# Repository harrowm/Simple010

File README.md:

# Simple010

A 68010 single-board computer based on the [rosco_m68k r2](https://github.com/rosco-m68k/rosco_m68k) design. Simple010 replaces the six discrete glue-logic ICs from that design with a single **ATF1508AS PLCC84 CPLD**, reducing board complexity while adding hardware SPI acceleration for SD card access.

## Hardware overview

| Item | Detail |
|------|--------|
| CPU | Motorola MC68010P at 10 MHz |
| RAM | 1 MB — two AS6C4008-55PCN SRAMs (even/odd byte lanes) |
| ROM | Two SST39SF040 4 Mb flash (even/odd byte lanes) |
| CPLD | ATF1508AS PLCC84 — replaces IC2/IC3/IC4/IC5/IC6/IC7 from rosco_m68k r2 |
| USB/serial | MCP2221A — USB-CDC serial to UART A. The original rosco_m68k board has two UARTs A and B. However, the code for two UARTs won't fit into the CPLD, so a cheaper one-channel USB-to-serial chip is used. |
| PCB | 4-layer, 100 × 100 mm, JLCPCB stackup (F.Cu / GND / PWR / B.Cu) |

### Memory map

| Range | Device |
|-------|--------|
| `$000000–$0FFFFF` | 1 MB SRAM |
| `$100000–$DFFFFF` | Expansion bus (DTACK from `LGEXP`) |
| `$E00000–$EFFFFF` | Flash ROM |
| `$F00000–$FFFFFF` | I/O — CPLD UART at `$F00000`, register select via A1–A4 |

### CPLD functional blocks

The CPLD (`code/cpld/cpld.v`) implements:

1. **Glue logic** — HALT/RESET open-drain drivers, CPU-space gating, boot flag
2. **Address decoder** — RAM, ROM, expansion, and I/O selects; DTACK; WR
3. **Watchdog** — 16-cycle timeout, asserts BERR open-drain
4. **UART A** — fixed 115200 8N1, XR68C681-compatible register map
5. **GPIO / OPR** — XR68C681 output port emulation; drives SPI CS, LEDs, MOSI, SCK
6. **SPI RX accelerator** — hardware-assisted SD card byte receive at ~1.843 MHz
7. **Interrupt priority encoder** — replaces 74LS148; encodes IRQ2/3/5/6 + UART RX into IPL2:1:0

Resource utilisation: **122/128 macro cells (95%)**.

## Repository layout

```
design/
  Simple010/            KiCad 10 schematic and PCB (1 MB SRAM)
    Simple010.kicad_sch   top-level (references four sub-sheets)
    CPU.kicad_sch         MC68010P, oscillator, expansion connector
    Memory.kicad_sch      SRAM, ROM, write-enable jumper
    CPLD.kicad_sch        ATF1508AS, JTAG header, LEDs, pull-ups
    USB.kicad_sch         MCP2221A, SD card, reset supervisor, power LEDs
    production/           Gerbers, BOM, position file
  Simple010-16/         KiCad 10 schematic and PCB (16 MB SRAM variant)
  datasheets/           component datasheets and parts index (INDEX.md)

code/cpld/       ATF1508AS Verilog RTL and testbench
  cpld.v                RTL source with //PIN: preassignment comments
  tb_cpld.v             testbench (120 assertions)
  build.sh              synthesis → fit → pin check → simulation
  cpld.jed              program this into the device
  cpld.fit / cpld.pin   fitter log and pin placement

rosco/           rosco_m68k firmware (git clone), modified for Simple010
```

## CPLD build

Requires [`atf15xx_yosys`](https://github.com/hoglet67/atf15xx_yosys.git) cloned into `~/atf15xx_yosys`, and `iverilog`/`vvp` on PATH.

```sh
cd code/cpld && ./build.sh
```

Expected output: `122/128 MCs used` and `120/120 tests passed`.

To run the testbench without re-synthesising:

```sh
cd code/cpld && iverilog -DSIMULATION -o tb_cpld tb_cpld.v cpld.v && vvp tb_cpld
```

The `-DSIMULATION` flag is required — without it 2 of 120 tests fail due to a cross-clock-domain handshake that behaves differently under deterministic simulation timing.

## Firmware

The firmware is the standard rosco_m68k r2 firmware cloned into `rosco/`, with minimal changes for Simple010 hardware.

The rosco directory is a clone of [rosco-m68k/rosco_m68k](https://github.com/rosco-m68k/rosco_m68k). Simple010 changes are on the `develop` branch, pushed to a fork at [harrowm/rosco_m68k](https://github.com/harrowm/rosco_m68k). The upstream is `origin`; the fork is `fork`:

```sh
cd rosco/rosco_m68k
git add <files>
git commit -m "description"
git push fork develop
```

### CPLD compatibility

The CPLD's UART emulates the XR68C681 (MC68681) at the register level. The existing rosco firmware DUART detection and initialisation code works without modification: the CPLD returns `0x0F` from the IVR register at reset, exactly as the real XR68C681 does.

### Simple010-specific changes

#### Startup detection — `stage1/main1.c`

At startup, after printing the standard CPU and memory information, the firmware reads the CPLD detection register and prints additional messages:

```
MC68010 CPU @ 10.0MHz with 1048576 bytes RAM
Simple010 CPLD v1 detected
  SPI RX accelerator present
```

**Detection mechanism:** reading byte address `0xF00005` (`DUART_R_MISR` in `machine.h`) returns a fixed capability byte from the CPLD:

| Bit | Mask | Meaning |
|-----|------|---------|
| 7 | `0x80` | CPLD present (always 1) |
| 6 | `0x40` | SPI RX accelerator available |
| 1–0 | `0x03` | Bitstream version (currently 1) |

The combined value is `0xC1`. On the original XR68C681, this register is MISR (masked interrupt status), which reads ~`0x00` at boot — so the detection is safe on original rosco hardware and the CPLD messages simply do not appear.

> **Address note:** the CPLD's `uart_sel` is gated on `~LDS` (lower data strobe), so the access must target the **odd** byte address `0xF00005`. Reading even address `0xF00004` (upper data strobe / UDS) will not reach the CPLD.

#### SPI RX accelerator — `stage1/blockdev/bbspi.c`

The CPLD includes a hardware SPI byte-receive engine clocked at ~1.843 MHz (UART_CLK ÷ 2), reducing per-byte bus traffic from ~24 cycles to 2 cycles compared to bit-banging.

`BBSPI_initialize()` detects the accelerator by reading `0xF00005` and caches the result in a `static bool cpld_spi_accel`. `BBSPI_recv_byte()` and `BBSPI_recv_buffer()` then dispatch on this flag:

**Accelerated receive sequence (per byte):**

| Step | Action | Address |
|------|--------|---------|
| 1 | Write any value to SPIRX register — triggers one 8-bit receive | `0xF00009` (write) |
| 2 | Poll SRA bit 2 (`spi_busy`) until clear | `0xF00003` (read) |
| 3 | Read received byte from SPIRX register | `0xF00009` (read) |

Send operations (`BBSPI_send_byte`, `BBSPI_send_buffer`) are unchanged — they continue to bit-bang through the CPLD GPIO, which is correct since the SD card protocol is heavily read-biased and transmit calls are infrequent. On original rosco hardware, `cpld_spi_accel` is `false` and both receive functions fall back to the existing bit-bang asm routines in `dua_spi_asm.asm`.

## Parts and ordering

See [`design/datasheets/INDEX.md`](design/datasheets/INDEX.md) for a full BOM with LCSC and Mouser part numbers.

Key sourcing notes:
- **ATF1508AS-15JU84** — not on LCSC; order from Microchip direct, Mouser (556-AF1508AS15JU84), or DigiKey
- **MC68010P** — EOL; source from eBay or second-hand market
- **SST39SF040 PLCC-32** — not stocked on LCSC; use Mouser (579-SST39SF040-70-4I-NHE)

## Acknowledgements

Simple010 is based on the [rosco_m68k](https://github.com/rosco-m68k/rosco_m68k) project by Ross Bamford and contributors. The schematic topology, memory map, and firmware are derived from the rosco_m68k r2 mainboard design.

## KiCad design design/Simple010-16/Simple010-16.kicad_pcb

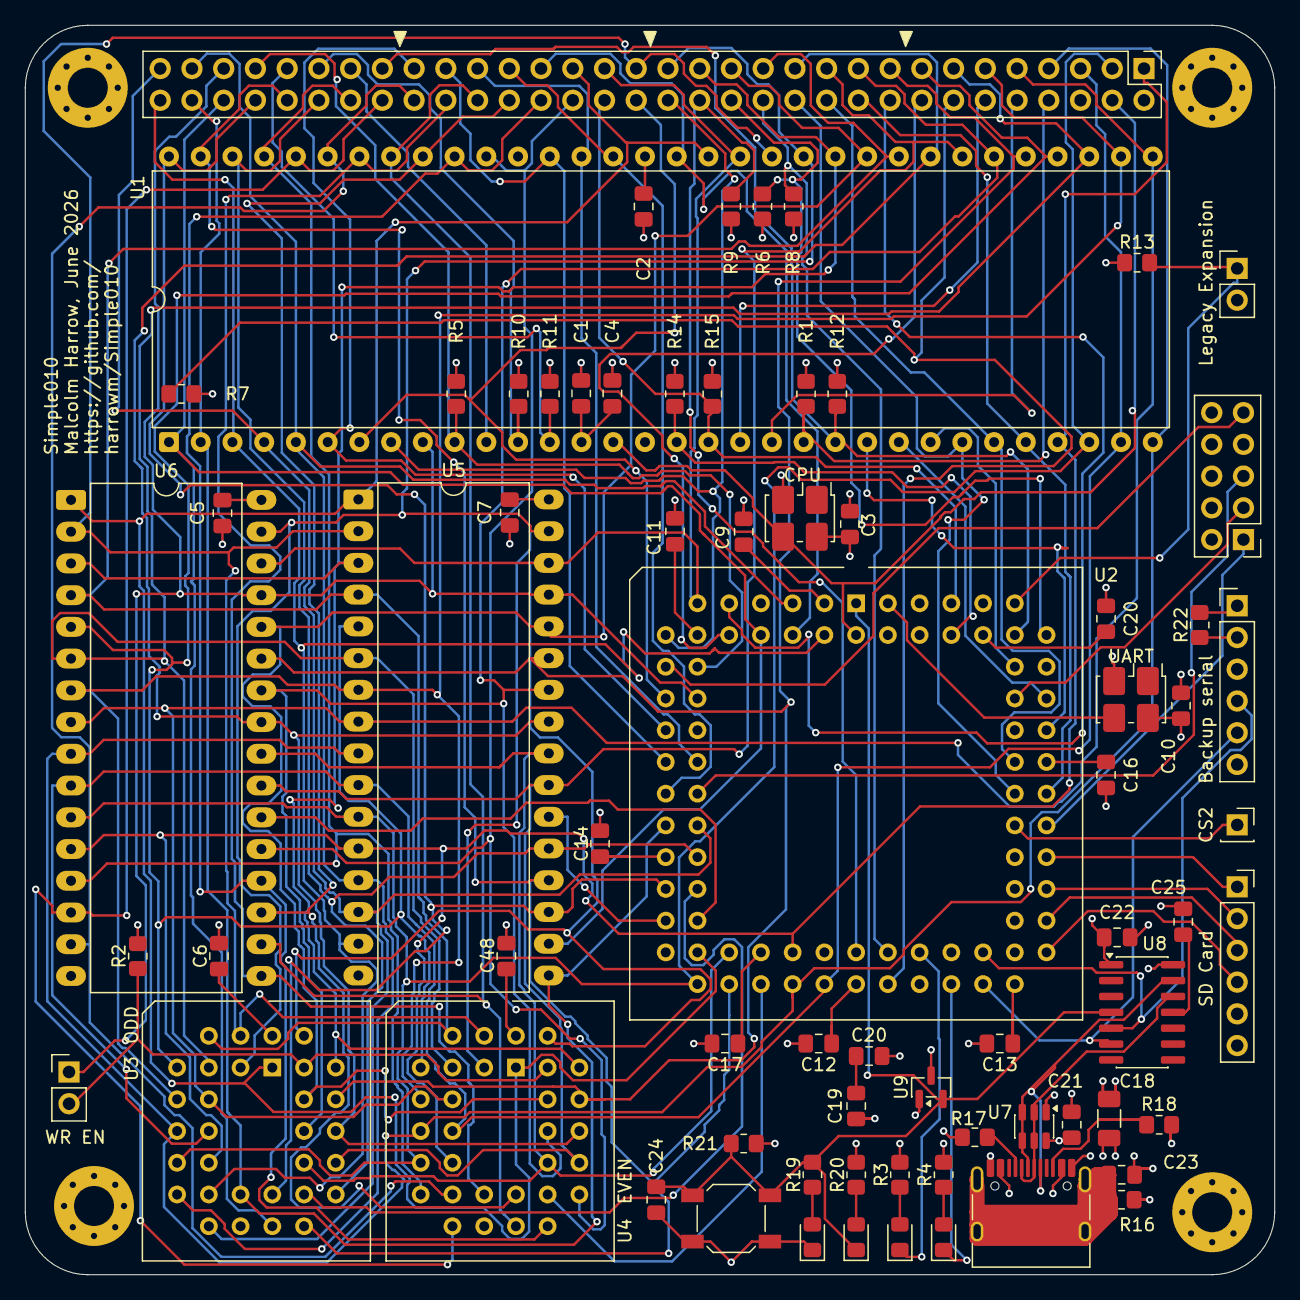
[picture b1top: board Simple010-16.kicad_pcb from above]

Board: 4 copper layers, 100.0 x 100.0 mm, 75 parts (0 on the bottom side), 102 nets.

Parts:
C1, C2, C3, C5, C6, C7, C8, C9, C10, C11, C12, C13, C14, C15, C16, C17, C20, C21, C22, C24: 100nF; C_0805_2012Metric_Pad1.18x1.45mm_HandSolder
C4, C19: 10uF; C_0805_2012Metric_Pad1.18x1.45mm_HandSolder
C18: 47uF; C_1206_3216Metric_Pad1.33x1.80mm_HandSolder
C23: 100pF; C_0805_2012Metric_Pad1.18x1.45mm_HandSolder
C25: 470nF; C_0805_2012Metric_Pad1.18x1.45mm_HandSolder
H1, H2, H3, H4: MountingHole_Pad; MountingHole_3.2mm_M3_Pad_Via
J1: CS2; PinSocket_1x01_P2.54mm_Vertical
J2: Conn_02x05_Odd_Even; PinHeader_2x05_P2.54mm_Vertical
J3: USB_C_Receptacle_USB2.0_16P; USB_C_Receptacle_HRO_TYPE-C-31-M-12
J4: Backup serial; PinHeader_1x06_P2.54mm_Vertical
J7: Conn_02x32_Odd_Even; PinHeader_2x32_P2.54mm_Vertical
J8: SD Card; PinSocket_1x06_P2.54mm_Vertical
JP1: ROM WR Enable; PinHeader_1x02_P2.54mm_Vertical
JP2: Legacy Expansion; PinHeader_1x02_P2.54mm_Vertical
LED1, LED3: GREEN; LED_0805_2012Metric_Pad1.15x1.40mm_HandSolder
LED2, LED4: RED; LED_0805_2012Metric_Pad1.15x1.40mm_HandSolder
R1, R2: 10K; R_0805_2012Metric_Pad1.20x1.40mm_HandSolder
R3, R4, R19, R20, R21: 1K; R_0805_2012Metric_Pad1.20x1.40mm_HandSolder
R5: 1K2; R_0805_2012Metric_Pad1.20x1.40mm_HandSolder
R6, R7, R8, R9, R10, R11, R12, R13, R14, R15, R22: 4K7; R_0805_2012Metric_Pad1.20x1.40mm_HandSolder
R16: 1M; R_0805_2012Metric_Pad1.20x1.40mm_HandSolder
R17, R18: 5.1k; R_0805_2012Metric_Pad1.20x1.40mm_HandSolder
SW1: Reset; SW_SPST_SKQG_WithoutStem
U1: MC68010P; DIP-64_W22.86mm
U2: ATF1508ASx-xxJx84; PLCC-84_THT-Socket
U3, U4: SST39SF040; PLCC-32_THT-Socket
U5, U6: AS6C4008-55PCN; DIP-32_W15.24mm_LongPads
U7: USBLC6-2SC6; SOT-23-6
U8: MCP2221A; SOIC-14_3.9x8.7mm_P1.27mm
U9: LM809M3-4.63/NOPB; SOT-23
Y1: SG-5032CAN 10MHz; Oscillator_SMD_SeikoEpson_SG8002LB-4Pin_5.0x3.2mm_HandSolde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
Y2: SG-5032CAN 3.6864MHz; Oscillator_SMD_SeikoEpson_SG8002LB-4Pin_5.0x3.2mm_HandSolde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

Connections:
A1: J7.1, U1.29 (A1), U2.40 (I/O), U3.12 (A0), U4.12 (A0), U5.12 (A0), U6.12 (A0)
A2: J7.3, U1.30 (A2), U2.33 (I/O), U3.11 (A1), U4.11 (A1), U5.11 (A1), U6.11 (A1)
A3: J7.5, U1.31 (A3), U2.41 (I/O), U3.10 (A2), U4.10 (A2), U5.10 (A2), U6.10 (A2)
A4: J7.7, U1.32 (A4), U2.39 (I/O), U3.9 (A3), U4.9 (A3), U5.9 (A3), U6.9 (A3)
A5: J7.9, U1.33 (A5), U3.8 (A4), U4.8 (A4), U5.8 (A4), U6.8 (A4)
A6: J7.11, U1.34 (A6), U3.7 (A5), U4.7 (A5), U5.7 (A5), U6.7 (A5)
A7: J7.13, U1.35 (A7), U3.6 (A6), U4.6 (A6), U5.6 (A6), U6.6 (A6)
A8: J7.15, U1.36 (A8), U3.5 (A7), U4.5 (A7), U5.5 (A7), U6.5 (A7)
A9: J7.17, U1.37 (A9), U3.27 (A8), U4.27 (A8), U5.27 (A8), U6.27 (A8)
A10: J7.19, U1.38 (A10), U3.26 (A9), U4.26 (A9), U5.26 (A9), U6.26 (A9)
A11: J7.21, U1.39 (A11), U3.23 (A10), U4.23 (A10), U5.23 (A10), U6.23 (A10)
A12: J7.23, U1.40 (A12), U3.25 (A11), U4.25 (A11), U5.25 (A11), U6.25 (A11)
A13: J7.25, U1.41 (A13), U3.4 (A12), U4.4 (A12), U5.4 (A12), U6.4 (A12)
A14: J7.27, U1.42 (A14), U3.28 (A13), U4.28 (A13), U5.28 (A13), U6.28 (A13)
A15: J7.29, U1.43 (A15), U3.29 (A14), U4.29 (A14), U5.3 (A14), U6.3 (A14)
A16: J7.31, U1.44 (A16), U3.3 (A15), U4.3 (A15), U5.31 (A15), U6.31 (A15)
A17: J7.33, U1.45 (A17), U3.2 (A16), U4.2 (A16), U5.2 (A16), U6.2 (A16)
A18: J7.35, U1.46 (A18), U2.11 (I/O), U3.30 (A17), U4.30 (A17), U5.30 (A17), U6.30 (A17)
A19: J7.37, U1.47 (A19), U2.34 (I/O), U3.1 (A18), U4.1 (A18), U5.1 (A18), U6.1 (A18)
A20: J7.39, U1.48 (A20), U2.6 (I/O)
A21: J7.41, U1.50 (A21), U2.22 (I/O)
A22: J7.43, U1.51 (A22), U2.21 (I/O)
A23: J7.45, U1.52 (A23), U2.20 (I/O)
AS: J7.47, U1.6 (~AS), U2.18 (I/O)
BERR: J7.49, R12.2, U1.22 (~BERR), U2.76 (I/O)
BG: J7.51, U1.11 (~BG)
BGACK: J7.53, R10.2, U1.12 (~BGACK)
BR: J7.55, R11.2, U1.13 (~BR)
CLK: J7.4, U1.15 (CLK), U2.2 (INPUT/OE2/GCLK2), Y1.3 (OUT)
D0: J7.61, U1.5 (D0), U2.5 (I/O), U3.13 (D0), U5.13 (DQ0)
D1: J7.63, U1.4 (D1), U2.25 (I/O), U3.14 (D1), U5.14 (DQ1)
D2: J7.64, U1.3 (D2), U2.4 (I/O), U3.15 (D2), U5.15 (DQ2)
D3: J7.62, U1.2 (D3), U2.24 (I/O), U3.17 (D3), U5.17 (DQ3)
D4: J7.60, U1.1 (D4), U2.8 (I/O), U3.18 (D4), U5.18 (DQ4)
D5: J7.58, U1.64 (D5), U2.28 (I/O), U3.19 (D5), U5.19 (DQ5)
D6: J7.56, U1.63 (D6), U2.35 (I/O), U3.20 (D6), U5.20 (DQ6)
D7: J7.54, U1.62 (D7), U2.27 (I/O), U3.21 (D7), U5.21 (DQ7)
D8: J7.52, U1.61 (D8), U4.13 (D0), U6.13 (DQ0)
D9: J7.50, U1.60 (D9), U4.14 (D1), U6.14 (DQ1)
D10: J7.48, U1.59 (D10), U4.15 (D2), U6.15 (DQ2)
D11: J7.46, U1.58 (D11), U4.17 (D3), U6.17 (DQ3)
D12: J7.44, U1.57 (D12), U4.18 (D4), U6.18 (DQ4)
D13: J7.42, U1.56 (D13), U4.19 (D5), U6.19 (DQ5)
D14: J7.40, U1.55 (D14), U4.20 (D6), U6.20 (DQ6)
D15: J7.38, U1.54 (D15), U4.21 (D7), U6.21 (DQ7)
DTACK: J7.57, R5.2, U1.10 (~DTACK), U2.15 (I/O)
E: J7.10, U1.20 (E)
EVENRAMSEL: U2.31 (I/O), U6.22 (CE#)
EVENROMSEL: U2.37 (I/O), U4.22 (CE)
EXPSEL: J7.18, U2.9 (I/O)
FC0: J7.20, U1.28 (FC0), U2.64 (I/O)
FC1: J7.22, U1.27 (FC1), U2.67 (I/O)
FC2: J7.24, U1.26 (FC2), U2.65 (I/O)
GND: C1.2, C2.2, C3.2, C4.2, C5.2, C6.2, C7.2, C8.2, C9.2, C10.2, C11.2, C12.2, C13.2, C14.2, C15.2, C16.2, C17.2, C18.2, C19.1, C21.2, C22.2, C23.2, C24.2, C25.1, H1.1 (1_1), H2.1 (1_1), H3.1 (1_1), H4.1 (1_1), J2.2, J2.10, J3.A1 (GND), J3.A12 (GND), J3.B1 (GND), J3.B12 (GND), J4.1, J7.6, J8.6, JP2.2 (B), LED1.1 (K), R16.2, R17.2, R18.2, R22.2, SW1.1, U1.16 (GND), U1.53 (GND), U2.7 (GND), U2.19 (GND), U2.32 (GND), U2.42 (GND), U2.47 (GND), U2.59 (GND), U2.72 (GND), U2.82 (GND), U3.16 (GND), U4.16 (GND), U5.16 (VSS), U6.16 (VSS), U7.1 (I/O1), U8.14 (VSS), U9.1 (GND), Y1.2 (GND), Y2.2 (GND)
GNDS: C23.1, J3.SH (SHIELD), R16.1
HALT: R14.2, U1.17 (~HALT), U2.80 (I/O)
HWRST: C24.1, LED2.1 (K), R19.1, R21.2, SW1.2, U2.1 (INPUT/GCLR), U8.4 (~RST), U9.2 (RESET)
IOSEL: J7.16, U2.10 (I/O)
IPL0: U1.25 (~IPL0), U2.73 (I/O)
IPL1: U1.24 (~IPL1), U2.70 (I/O)
IPL2: U1.23 (~IPL2), U2.68 (I/O)
IRQ2: J7.28, R6.2, U2.74 (I/O)
IRQ3: J7.14, R7.2, U2.45 (I/O/PD2)
IRQ5: J7.26, R8.2, U2.46 (I/O)
IRQ6: J7.30, R9.2, U2.44 (I/O)
LDS: J7.32, U1.8 (~LDS), U2.12 (I/O/PD1)
LED_GREEN: LED3.1 (K), U2.48 (I/O)
LED_RED: LED4.1 (K), U2.49 (I/O)
LGEXP: JP2.1 (A), R13.2, U2.75 (I/O)
unnamed: C19.2, C20.1
unnamed: J3.A5 (CC1), R17.1
unnamed: J3.B5 (CC2), R18.1
unnamed: J4.2, R22.1
unnamed: LED1.2 (A), R19.2
unnamed: LED2.2 (A), R20.2
unnamed: LED3.2 (A), R3.2
unnamed: LED4.2 (A), R4.2
unnamed: C25.2, U8.11 (VUSB)
ODDRAMSEL: U2.30 (I/O), U5.22 (CE#)
ODDROMSEL: U2.29 (I/O), U3.22 (CE)
RESET: J7.36, R15.2, U1.18 (~RESET), U2.79 (I/O)
ROM_RW: JP1.2 (B), R2.2, U3.31 (PGM), U4.31 (PGM)
RW: J7.59, JP1.1 (A), U1.9 (R/~W), U2.17 (I/O), U5.29 (WE#), U6.29 (WE#)
RXDA: J4.4, U2.52 (I/O), U8.5 (URx)
SPICLK: J8.2, U2.58 (I/O)
SPICS: J8.1, U2.60 (I/O)
SPICS2: J1.1 (Pin_1_1), U2.63 (I/O)
SPIMISO: J8.4, U2.54 (I/O)
SPIMOSI: J8.3, U2.56 (I/O)
TCK: J2.1, U2.62 (I/O/TCK)
TDI: J2.9, U2.14 (I/O/TDI)
TDO: J2.3, U2.71 (I/O/TDO)
TMS: J2.5, U2.23 (I/O/TMS)
TXDA: J4.5, U2.51 (I/O), U8.6 (UTx)
UART_CLK: U2.83 (INPUT/GCLK1), Y2.3 (OUT)
UDS: J7.34, U1.7 (~UDS), U2.16 (I/O)
USB_N: J3.A7 (D-), J3.B7 (D-), U7.2 (GND), U7.5 (VBUS), U8.12 (D-)
USB_P: J3.A6 (D+), J3.B6 (D+), U7.3 (I/O2), U7.4 (I/O2), U8.13 (D+)
VCC: C1.1, C2.1, C3.1, C4.1, C5.1, C6.1, C7.1, C8.1, C9.1, C10.1, C11.1, C12.1, C13.1, C14.1, C15.1, C16.1, C17.1, C18.1, C20.2, C21.1, C22.1, J2.4, J3.A4 (VBUS), J3.A9 (VBUS), J3.B4 (VBUS), J3.B9 (VBUS), J4.3, J7.2, J8.5, R1.1, R2.1, R3.1, R4.1, R5.1, R6.1, R7.1, R8.1, R9.1, R10.1, R11.1, R12.1, R13.1, R14.1, R15.1, R20.1, R21.1, U1.14 (V_{CC}), U1.49 (V_{CC}), U2.3 (VCCINT), U2.13 (VCCIO), U2.26 (VCCIO), U2.38 (VCCIO), U2.43 (VCCINT), U2.53 (VCCIO), U2.66 (VCCIO), U2.78 (VCCIO), U3.32 (VCC), U4.32 (VCC), U5.32 (VCC), U6.32 (VCC), U7.6 (I/O1), U8.1 (VDD), U9.3 (V_{DD}), Y1.4 (VCC), Y2.4 (VCC)
VMA: J7.12, U1.19 (~VMA)
VPA: J7.8, R1.2, U1.21 (~VPA)
WR: U2.36 (I/O), U3.24 (OE), U4.24 (OE), U5.24 (OE#), U6.24 (OE#)

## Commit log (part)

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2026-06-02 Sort out R and C types
2026-06-03 Clean ERCC on schmatic
2026-06-17 Further improvements on CPLD pin placement to improve routing
2026-06-17 Create one build script for the cpld verliog code and testbench
